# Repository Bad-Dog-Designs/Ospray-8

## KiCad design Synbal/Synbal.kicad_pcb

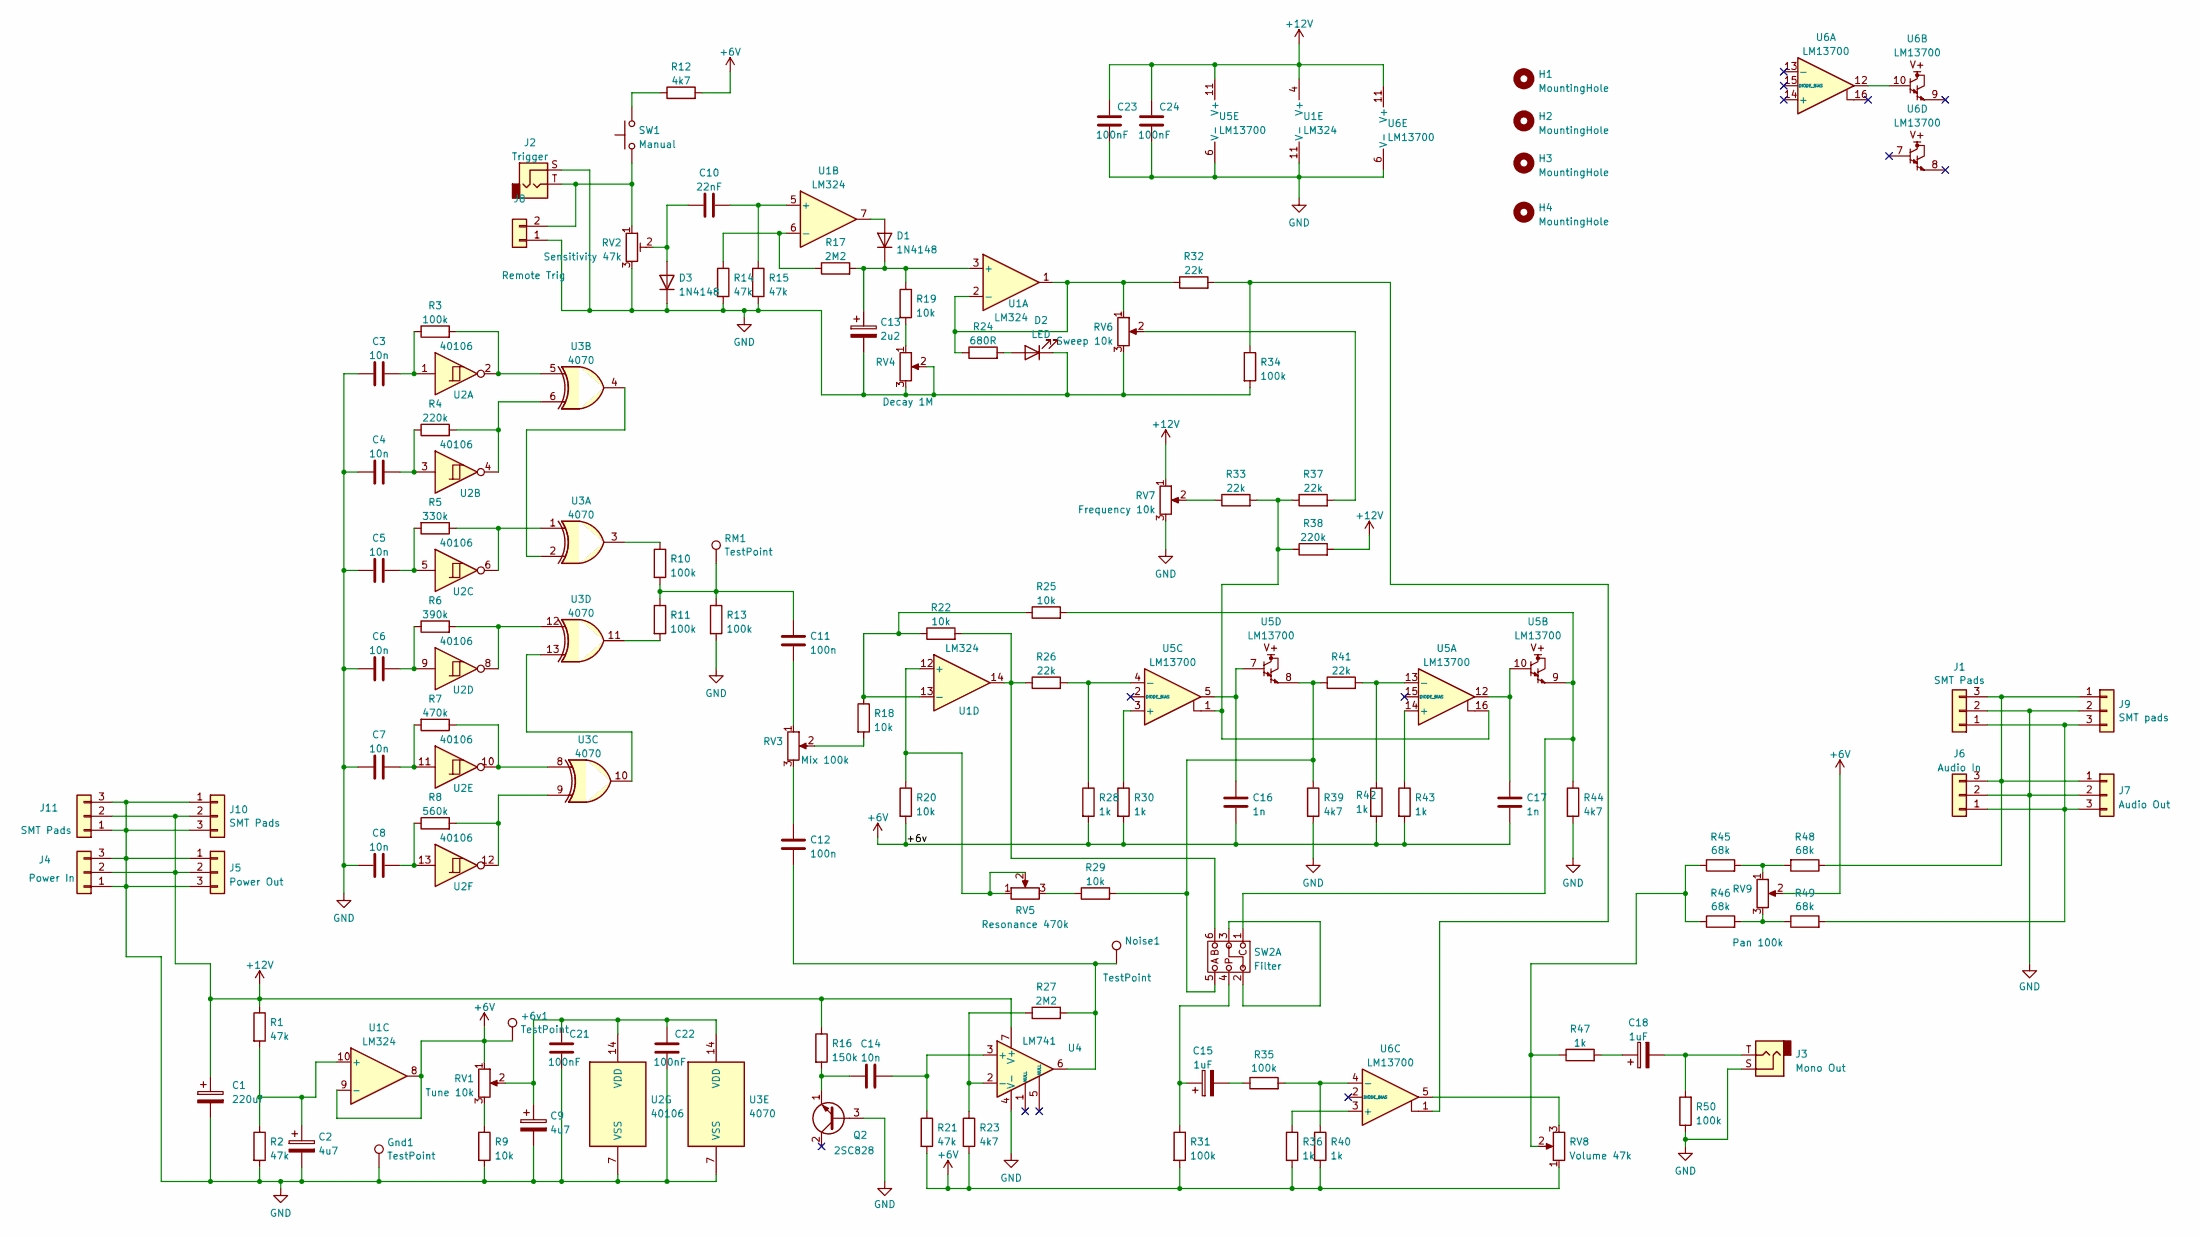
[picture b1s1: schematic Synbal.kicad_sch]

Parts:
+6v1: TestPoint; TestPoint_Keystone_5010-5014_Multipurpose
C1: 220uf; CP_Radial_D8.0mm_P3.50mm
C2, C9: 4u7; CP_Radial_D4.0mm_P1.50mm
C3, C4, C5, C6, C7, C8, C14: 10n; C_Disc_D7.0mm_W2.5mm_P5.00mm
C10: 22nF; C_Disc_D7.0mm_W2.5mm_P5.00mm
C11, C12: 100n; C_Disc_D7.0mm_W2.5mm_P5.00mm
C13: 2u2; CP_Radial_D4.0mm_P1.50mm
C15, C18: 1uF; CP_Radial_D4.0mm_P1.50mm
C16, C17: 1n; C_Disc_D7.0mm_W2.5mm_P5.00mm
C21, C22, C23, C24: 100nF; C_0805_2012Metric
D1, D3: 1N4148; D_MiniMELF
D2: LED; LED_D3.0mm
Gnd1: TestPoint; TestPoint_Keystone_5010-5014_Multipurpose
H1, H2, H3, H4: MountingHole; MountingHole_3.2mm_M3_ISO7380_Pad
J1, J10, J11: SMT Pads; Bus Connector
J2: Trigger; Jack_3.5mm_QingPu_WQP-PJ398SM_Vertical_CircularHoles
J3: Mono Out; Jack_3.5mm_QingPu_WQP-PJ398SM_Vertical_CircularHoles
J4: Power In; PinHeader_1x03_P2.54mm_Horizontal
J5: Power Out; PinHeader_1x03_P2.54mm_Horizontal
J6: Audio In; PinHeader_1x03_P2.54mm_Horizontal
J7: Audio Out; PinHeader_1x03_P2.54mm_Horizontal
J8: Remote Trig; PinHeader_1x02_P2.54mm_Vertical
J9: SMT pads; Bus Connector
Noise1: TestPoint; TestPoint_Keystone_5010-5014_Multipurpose
Q2: 2SC828; TO-92_Inline
R1, R2, R14, R15, R21: 47k; R_1206_3216Metric
R3, R10, R11, R13, R31, R34, R35, R50: 100k; R_1206_3216Metric
R4, R38: 220k; R_1206_3216Metric
R5: 330k; R_1206_3216Metric
R6: 390k; R_1206_3216Metric
R7: 470k; R_1206_3216Metric
R8: 560k; R_1206_3216Metric
R9, R18, R19, R20, R22, R25, R29: 10k; R_1206_3216Metric
R12, R23, R39, R44: 4k7; R_1206_3216Metric
R16: 150k; R_1206_3216Metric
R17, R27: 2M2; R_1206_3216Metric
R24: 680R; R_1206_3216Metric
R26, R32, R33, R37, R41: 22k; R_1206_3216Metric
R28, R30, R36, R40, R42, R43, R47: 1k; R_1206_3216Metric
R45, R46, R48, R49: 68k; R_1206_3216Metric
RM1: TestPoint; TestPoint_Keystone_5010-5014_Multipurpose
RV1: Tune 10k; Potentiometer_Alps_RK09K_Single_Vertical
RV2: Sensitivity 47k; Potentiometer_Piher_PT-6-V_Vertical
RV3: Mix 100k; Potentiometer_Alps_RK09K_Single_Vertical
RV4: Decay 1M; Potentiometer_Alps_RK09K_Single_Vertical
RV5: Resonance 470k; Potentiometer_Alps_RK09K_Single_Vertical
RV6: Sweep 10k; Potentiometer_Alps_RK09K_Single_Vertical
RV7: Frequency 10k; Potentiometer_Alps_RK09K_Single_Vertical
RV8: Volume 47k; Potentiometer_Alps_RK09K_Single_Vertical
RV9: Pan 100k; Potentiometer_Alps_RK09K_Single_Vertical
SW1: Manual; SW_PUSH_6mm_H5mm
SW2: Filter; 1P3WSW
U1: LM324; SOIC-14_3.9x8.7mm_P1.27mm
U2: 40106; SO-14_3.9x8.65mm_P1.27mm
U3: 4070; SO-14_3.9x8.65mm_P1.27mm
U4: LM741; SOIC-8_3.9x4.9mm_P1.27mm
U5, U6: LM13700; SOIC-16_3.9x9.9mm_P1.27mm

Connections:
+6V: +6v1.1, C16.2, C17.2, R12.2, R20.2, R21.2, R23.2, R28.2, R30.2, R31.2, R36.2, R40.2, R42.2, R43.2, RV1.1, RV8.1, RV9.2, U1.8, U1.9 (-); also elsewhere on the board
+12V: C1.1, C23.1, C24.1, J4.2, J5.2, J10.2, J11.2, R1.1, R16.1, R38.2, RV7.1, U1.4 (V+), U4.7 (V+), U5.11 (V+), U6.11 (V+)
GND: C1.2, C2.2, C3.1, C4.1, C5.1, C6.1, C7.1, C8.1, C9.2, C13.2, C21.2, C22.2, C23.2, C24.2, D2.1 (K), D3.1 (K), Gnd1.1, H1.1, H2.1, H3.1, H4.1, J1.2, J2.S, J3.S, J4.1, J4.3, J5.1, J5.3, J6.2, J7.2, J8.1, J9.2, J10.1, J10.3, J11.1, J11.3, Q2.3 (B), R2.2, R9.2, R13.2, R14.2, R15.2, R34.2, R39.2, R44.2, R50.1, RV1.MP, RV2.3, RV3.MP, RV4.2, RV4.3, RV4.MP, RV5.MP, RV6.3, RV6.MP, RV7.3, RV7.MP, RV8.MP, RV9.MP, U1.11 (V-), U2.7 (VSS), U3.7 (VSS), U4.4 (V-), U5.6 (V-), U6.6 (V-); also elsewhere on the board
unnamed: C3.2, R3.1, U2.1
unnamed: C4.2, R4.1, U2.3
unnamed: C5.2, R5.2, U2.5
unnamed: C6.2, R6.1, U2.9
unnamed: C7.2, R7.2, U2.11
unnamed: C8.2, R8.1, U2.13
unnamed 9: C11.1, R10.2, R11.1, R13.1, RM1.1; also elsewhere on the board
unnamed: C11.2, RV3.1
unnamed: C12.1, RV3.3
unnamed 12: C12.2, Noise1.1, R27.2, U4.6; also elsewhere on the board
unnamed: C15.1, R31.1, SW2.4
unnamed: C15.2, R35.1
unnamed: C16.1, U5.5, U5.7
unnamed: C17.1, U5.10, U5.12
unnamed: C18.1, R47.2
unnamed: C18.2, J3.T, R50.2
unnamed: D1.2 (A), U1.7
unnamed: C13.1, D1.1 (K), R17.2, R19.1, U1.3 (+)
unnamed: D2.2 (A), R24.2
unnamed: C10.1, D3.2 (A), RV2.2
unnamed: J1.1, J6.1, J7.3, J9.3, R49.2
unnamed: J1.3, J6.3, J7.1, J9.1, R48.1
unnamed: J2.T, J8.2, RV2.1, SW1.1
unnamed: C14.1, Q2.1 (E), R16.2
unnamed: R3.2, U2.2, U3.5
unnamed: R4.2, U2.4, U3.6
unnamed: R5.1, U2.6, U3.1
unnamed: R6.2, U2.8, U3.12
unnamed: R7.1, U2.10, U3.8
unnamed: R8.2, U2.12, U3.9
unnamed: R9.1, RV1.3
unnamed: R10.1, U3.3
unnamed: R11.2, U3.11
unnamed: R12.1, SW1.2
unnamed: R18.2, RV3.2
unnamed: R19.2, RV4.1
unnamed: R22.2, R26.1, SW2.6, U1.14
unnamed: R25.2, R44.1, SW2.1, U5.9
unnamed: R29.1, RV5.3
unnamed: R29.2, R39.1, R41.1, SW2.5, U5.8
unnamed: R32.2, R34.1, U6.1
unnamed: R33.1, RV7.2
unnamed: R33.2, R37.1, R38.1, U5.1, U5.16
unnamed: R37.2, RV6.2
unnamed: R45.1, R46.1, R47.1, RV8.2
unnamed: R45.2, R48.2, RV9.1
unnamed: R46.2, R49.1, RV9.3
unnamed: RV8.3, U6.5
unnamed: SW2.2, SW2.3
unnamed: R24.1, R32.1, RV6.1, U1.1, U1.2 (-)
unnamed: C10.2, R15.1, U1.5 (+)
unnamed: R14.1, R17.1, U1.6 (-)
unnamed: C2.1, R1.2, R2.1, U1.10 (+)
unnamed: R20.1, RV5.1, RV5.2, U1.12 (+)
unnamed: R18.1, R22.1, R25.1, U1.13 (-)
unnamed: C9.1, C21.1, C22.1, RV1.2, U2.14 (VDD), U3.14 (VDD)
unnamed: U3.2, U3.4
unnamed: U3.10, U3.13
unnamed: C14.2, R21.1, U4.3 (+)
unnamed: R23.1, R27.1, U4.2 (-)
unnamed: R43.1, U5.14 (+)
unnamed: R41.2, R42.1, U5.13 (-)
unnamed: R30.1, U5.3 (+)
unnamed: R26.2, R28.1, U5.4 (-)
unnamed: U6.10, U6.12
unnamed: R36.1, U6.3 (+)
unnamed: R35.2, R40.1, U6.4 (-)

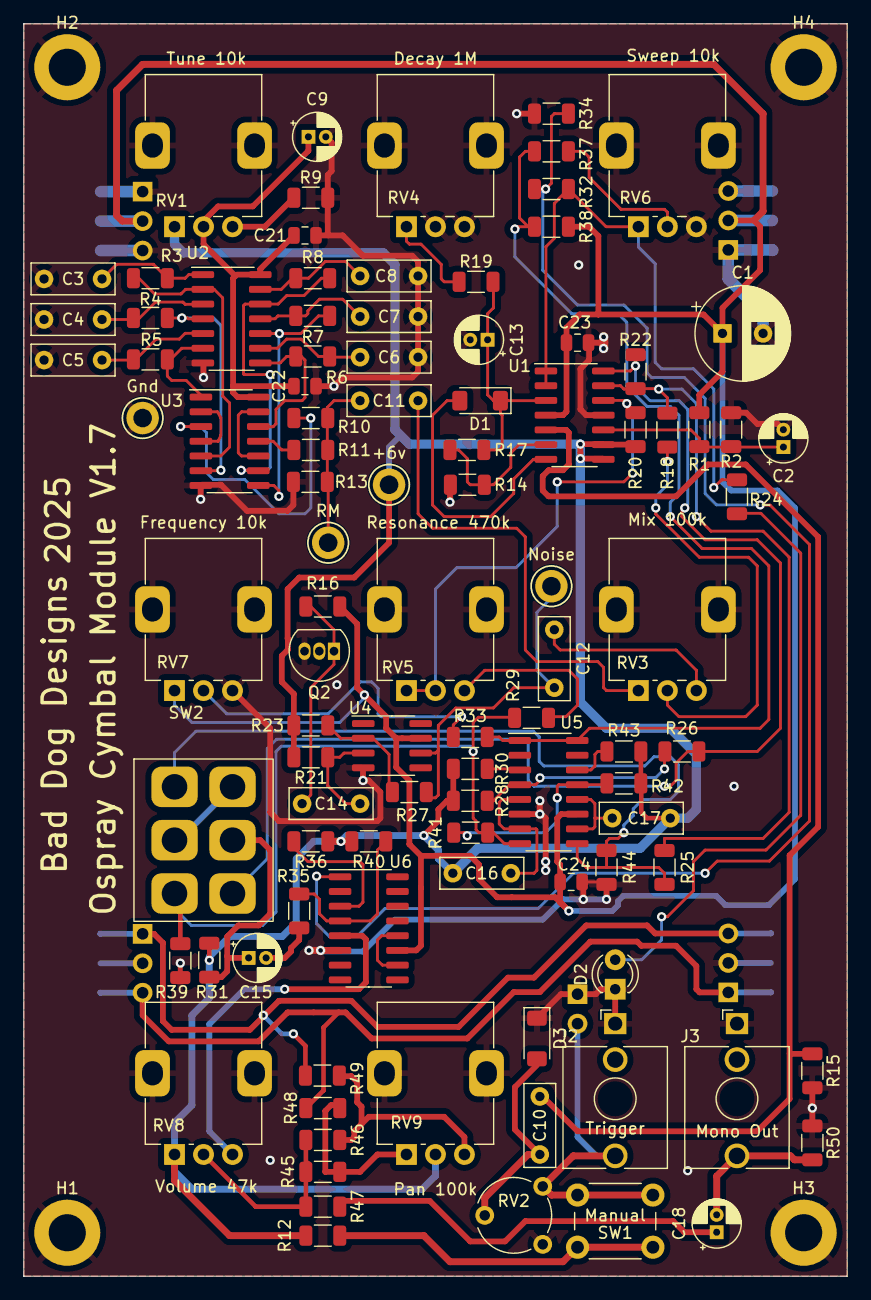
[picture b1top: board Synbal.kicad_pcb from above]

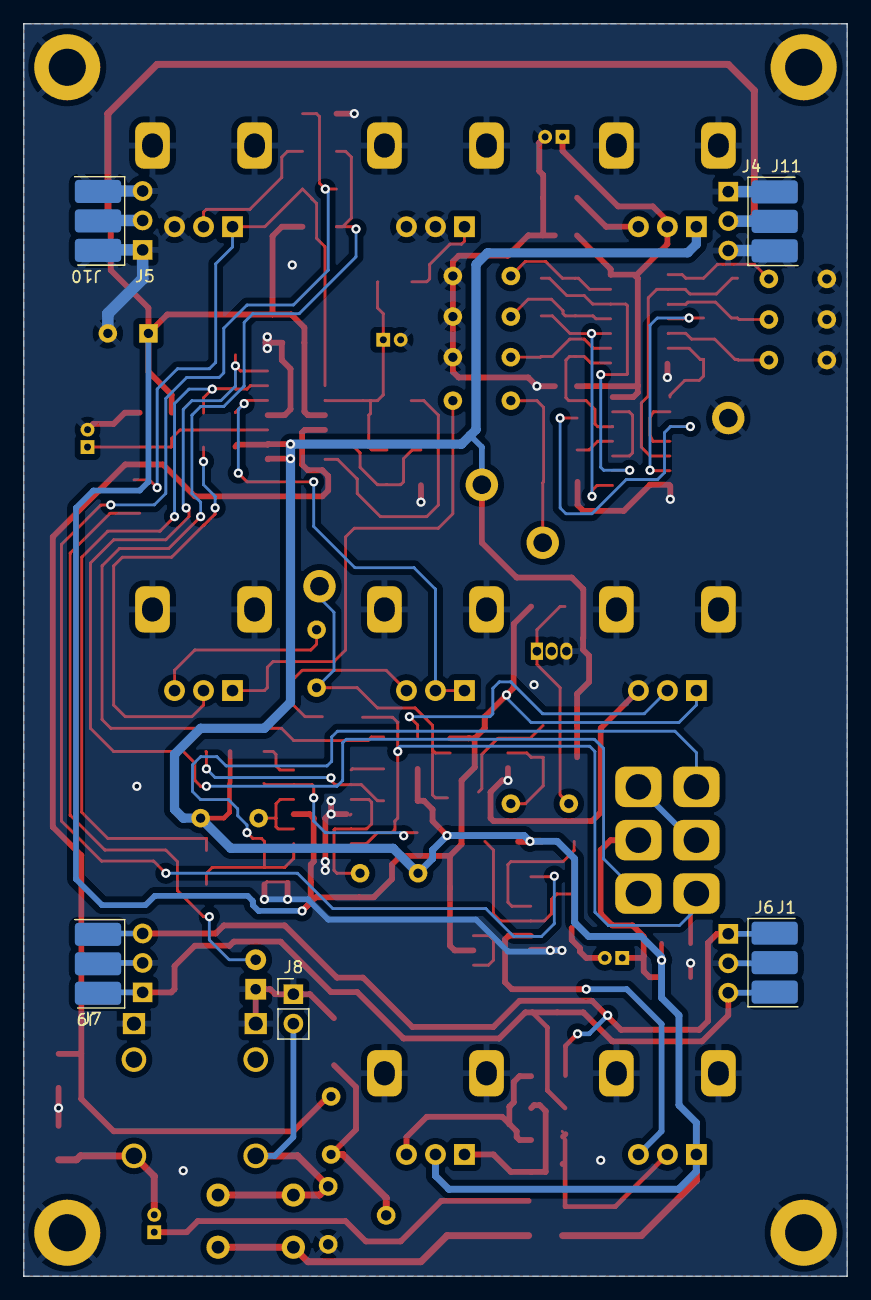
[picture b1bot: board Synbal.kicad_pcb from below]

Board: 2 copper layers, 71.0 x 108.0 mm, 112 parts (9 on the bottom side), 70 nets.

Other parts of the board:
+6v: TestPoint; TestPoint_Keystone_5010-5014_Multipurpose
Gnd: TestPoint; TestPoint_Keystone_5010-5014_Multipurpose
Noise: TestPoint; TestPoint_Keystone_5010-5014_Multipurpose
RM: TestPoint; TestPoint_Keystone_5010-5014_Multipurpose

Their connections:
+6V: +6v.1; also elsewhere on the board
GND: Gnd.1; also elsewhere on the board
unnamed 9: RM.1; also elsewhere on the board
unnamed 12: Noise.1; also elsewhere on the board

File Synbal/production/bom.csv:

Designator,Footprint,Quantity,Value,LCSC Part #
"+6V, GND, NOISE, RM",TestPoint_Keystone_5010-5014_Multipurpose,4,TestPoint,
C1,CP_Radial_D8.0mm_P3.50mm,1,220uf,
C10,C_Disc_D7.0mm_W2.5mm_P5.00mm,1,22nF,
"C11, C12",C_Disc_D7.0mm_W2.5mm_P5.00mm,2,100n,
C13,CP_Radial_D4.0mm_P1.50mm,1,2u2,
"C14, C3, C4, C5, C6, C7, C8",C_Disc_D7.0mm_W2.5mm_P5.00mm,7,10n,
"C15, C18",CP_Radial_D4.0mm_P1.50mm,2,1uF,
"C16, C17",C_Disc_D7.0mm_W2.5mm_P5.00mm,2,1n,
"C2, C9",CP_Radial_D4.0mm_P1.50mm,2,4u7,
"C21, C22, C23, C24",0805,4,100nF,
"D1, D3",D_MiniMELF,2,1N4148,
D2,LED_D3.0mm,1,LED,
"H1, H2, H3, H4",MountingHole_3.2mm_M3_ISO7380_Pad,4,MountingHole,
"J1, J10, J11, J9",Bus Connector,4,SMT Pads,
J2,Jack_3.5mm_QingPu_WQP-PJ398SM_Vertical_CircularHoles,1,Trigger,
J3,Jack_3.5mm_QingPu_WQP-PJ398SM_Vertical_CircularHoles,1,Mono Out,
J4,PinHeader_1x03_P2.54mm_Horizontal,1,Power In,
J5,PinHeader_1x03_P2.54mm_Horizontal,1,Power Out,
J6,PinHeader_1x03_P2.54mm_Horizontal,1,Audio In,
J7,PinHeader_1x03_P2.54mm_Horizontal,1,Audio Out,
J8,PinHeader_1x02_P2.54mm_Vertical,1,Remote Trig,
Q2,TO-92_Inline,1,2SC828,
"R1, R14, R15, R2, R21",1206,5,47k,
"R10, R11, R13, R3, R31, R34, R35, R50",1206,8,100k,
"R12, R23, R39, R44",1206,4,4k7,
R16,1206,1,150k,
"R17, R27",1206,2,2M2,
"R18, R19, R20, R22, R25, R29, R9",1206,7,10k,
R24,1206,1,680R,
"R26, R32, R33, R37, R41",1206,5,22k,
"R28, R30, R36, R40, R42, R43, R47",1206,7,1k,
"R38, R4",1206,2,220k,
"R45, R46, R48, R49",1206,4,68k,
R5,1206,1,330k,
R6,1206,1,390k,
R7,1206,1,470k,
R8,1206,1,560k,
RV1,Potentiometer_Alps_RK09K_Single_Vertical,1,Tune 10k,
RV2,Potentiometer_Piher_PT-6-V_Vertical,1,Sensitivity 47k,
RV3,Potentiometer_Alps_RK09K_Single_Vertical,1,Mix 100k,
RV4,Potentiometer_Alps_RK09K_Single_Vertical,1,Decay 1M,
RV5,Potentiometer_Alps_RK09K_Single_Vertical,1,Resonance 470k,
RV6,Potentiometer_Alps_RK09K_Single_Vertical,1,Sweep 10k,
RV7,Potentiometer_Alps_RK09K_Single_Vertical,1,Frequency 10k,
RV8,Potentiometer_Alps_RK09K_Single_Vertical,1,Volume 47k,
RV9,Potentiometer_Alps_RK09K_Single_Vertical,1,Pan 100k,
SW1,SW_PUSH_6mm_H5mm,1,Manual,
SW2,1P3WSW,1,Filter,
U1,SOIC-14_3.9x8.7mm_P1.27mm,1,LM324,
U2,SO-14_3.9x8.65mm_P1.27mm,1,40106,
U3,SO-14_3.9x8.65mm_P1.27mm,1,4070,
U4,SOIC-8_3.9x4.9mm_P1.27mm,1,LM741,
"U5, U6",SOIC-16_3.9x9.9mm_P1.27mm,2,LM13700,

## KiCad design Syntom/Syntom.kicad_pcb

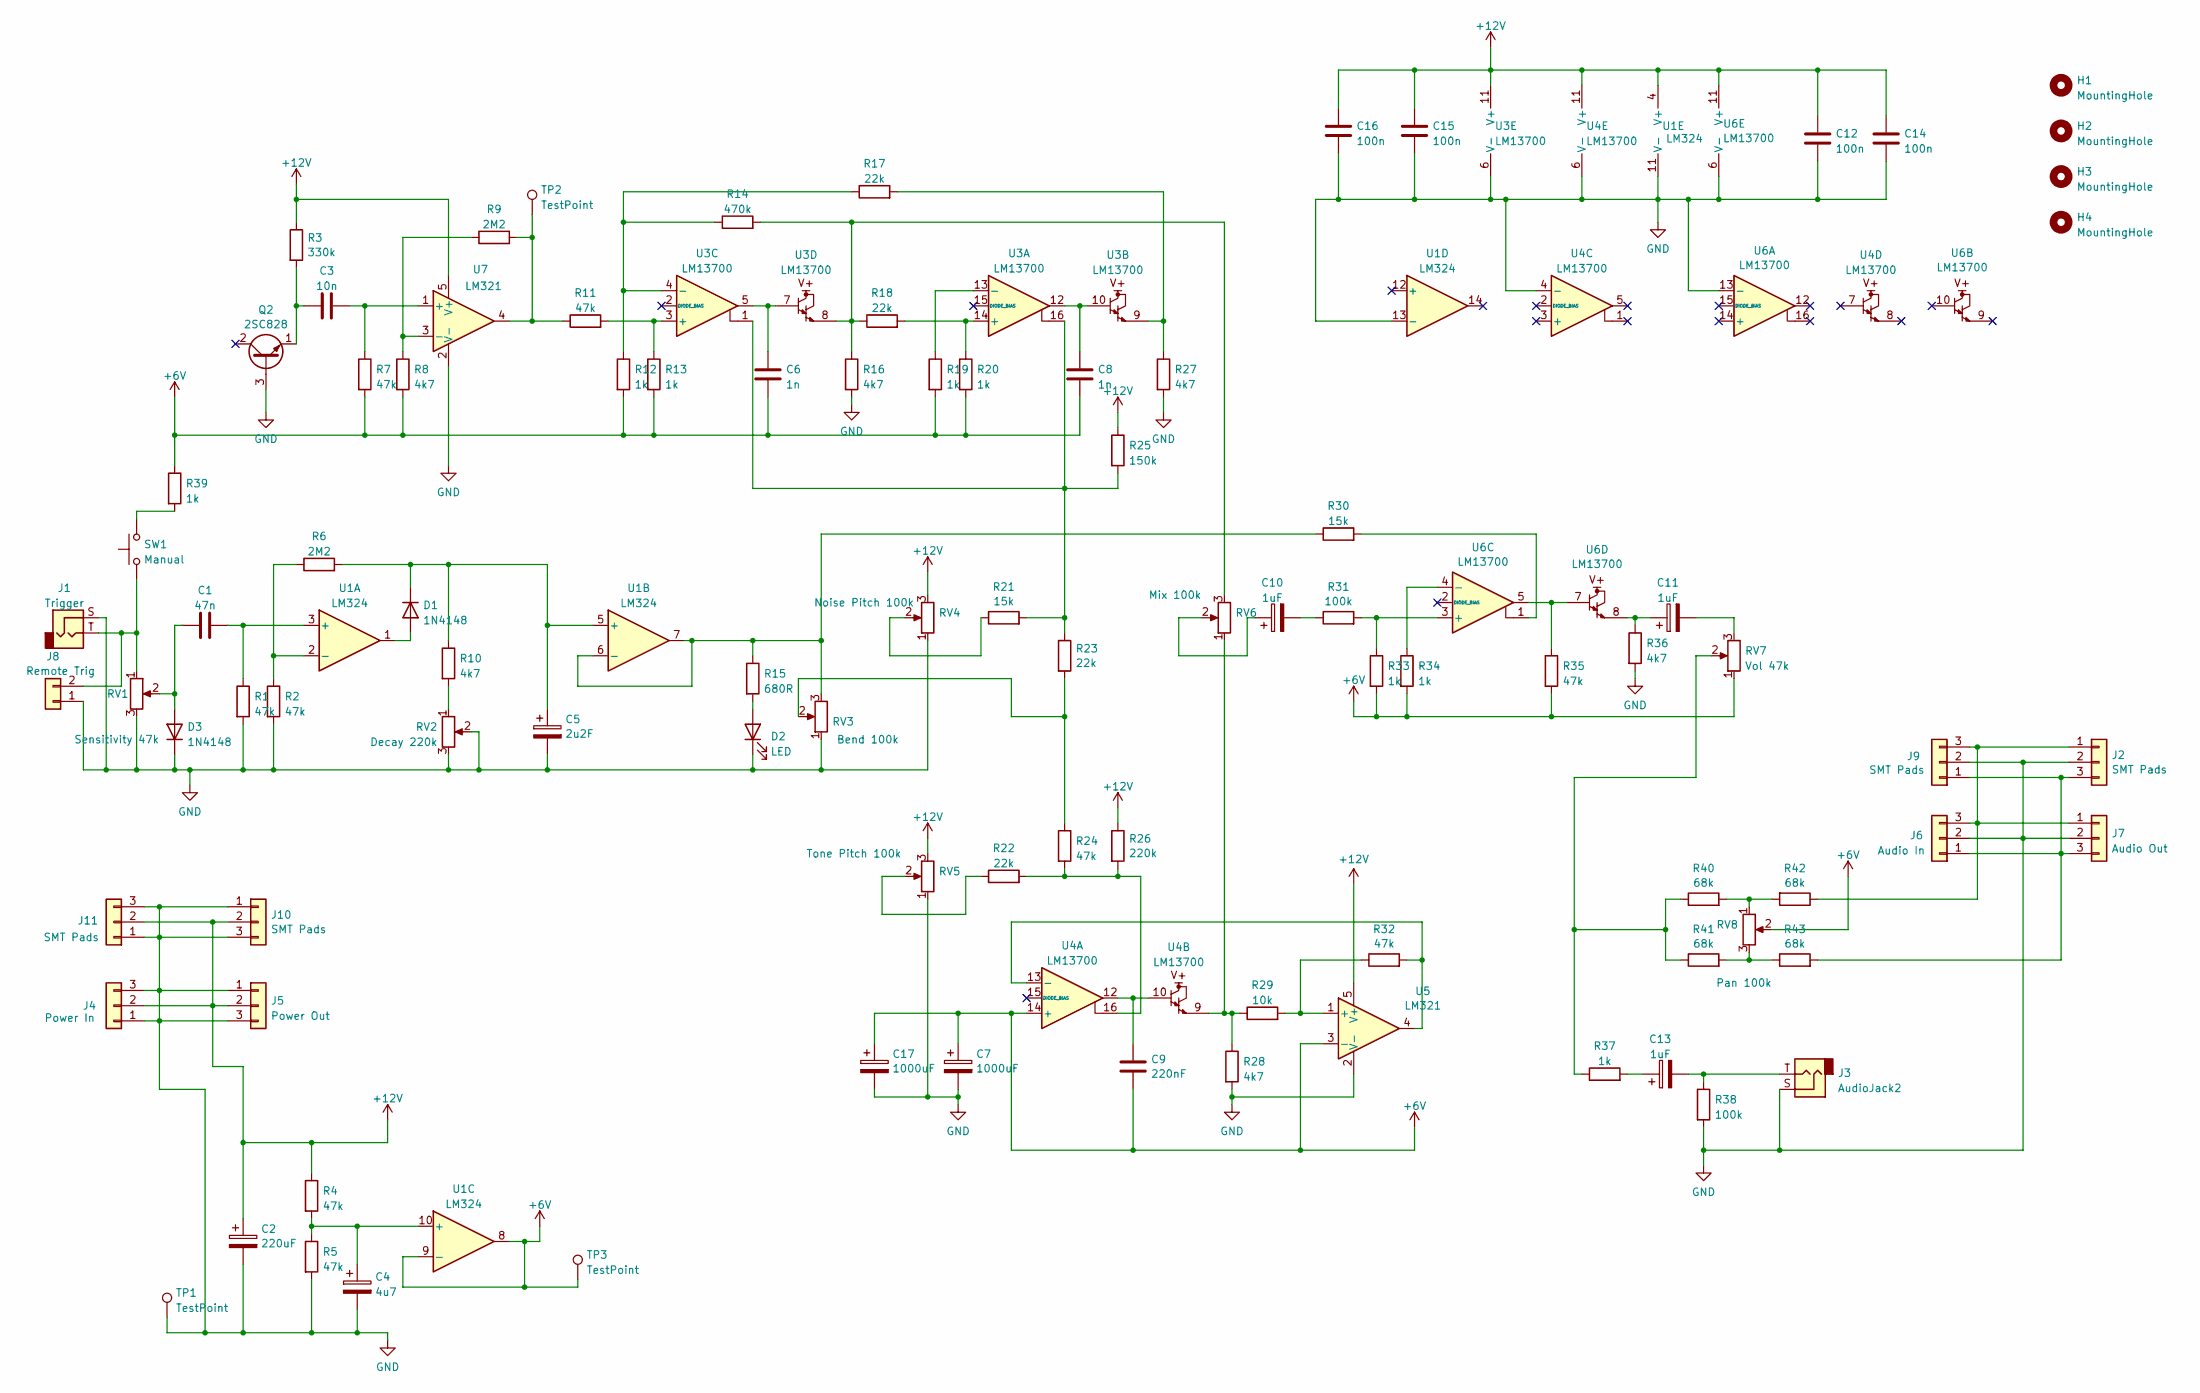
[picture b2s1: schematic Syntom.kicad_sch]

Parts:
C1: 47n; C_Disc_D4.3mm_W1.9mm_P5.00mm
C2: 220uF; CP_Radial_D8.0mm_P3.50mm
C3: 10n; C_Disc_D4.3mm_W1.9mm_P5.00mm
C4: 4u7; CP_Radial_D4.0mm_P1.50mm
C5: 2u2F; CP_Radial_D4.0mm_P1.50mm
C6, C8: 1n; C_Disc_D4.3mm_W1.9mm_P5.00mm
C7, C17: 1000uF; CP_Radial_D8.0mm_P3.50mm
C9: 220nF; C_Disc_D4.3mm_W1.9mm_P5.00mm
C10, C11, C13: 1uF; CP_Radial_D4.0mm_P1.50mm
C12, C14, C15, C16: 100n; C_0805_2012Metric
D1, D3: 1N4148; D_MiniMELF
D2: LED; LED_D3.0mm
H1, H2, H3, H4: MountingHole; MountingHole_3.2mm_M3_DIN965_Pad
J1: Trigger; Jack_3.5mm_QingPu_WQP-PJ398SM_Vertical_CircularHoles
J2, J9, J10, J11: SMT Pads; Bus Connector
J3: AudioJack2; Jack_3.5mm_QingPu_WQP-PJ398SM_Vertical_CircularHoles
J4: Power In; PinHeader_1x03_P2.54mm_Horizontal
J5: Power Out; PinHeader_1x03_P2.54mm_Horizontal
J6: Audio In; PinHeader_1x03_P2.54mm_Horizontal
J7: Audio Out; PinHeader_1x03_P2.54mm_Horizontal
J8: Remote Trig; PinHeader_1x02_P2.54mm_Vertical
Q2: 2SC828; TO-92_Inline
R1, R2, R4, R5, R7, R11, R24, R32, R35: 47k; R_1206_3216Metric
R3: 330k; R_1206_3216Metric
R6, R9: 2M2; R_1206_3216Metric
R8, R10, R16, R27, R28, R36: 4k7; R_1206_3216Metric
R12, R13, R19, R20, R33, R34, R37, R39: 1k; R_1206_3216Metric
R14: 470k; R_1206_3216Metric
R15: 680R; R_1206_3216Metric
R17, R18, R22, R23: 22k; R_1206_3216Metric
R21, R30: 15k; R_1206_3216Metric
R25: 150k; R_1206_3216Metric
R26: 220k; R_1206_3216Metric
R29: 10k; R_1206_3216Metric
R31, R38: 100k; R_1206_3216Metric
R40, R41, R42, R43: 68k; R_1206_3216Metric
RV1: Sensitivity 47k; Potentiometer_Piher_PT-6-V_Vertical
RV2: Decay 220k; Potentiometer_Alps_RK09K_Single_Vertical
RV3: Bend 100k; Potentiometer_Alps_RK09K_Single_Vertical
RV4: Noise Pitch 100k; Potentiometer_Alps_RK09K_Single_Vertical
RV5: Tone Pitch 100k; Potentiometer_Alps_RK09K_Single_Vertical
RV6: Mix 100k; Potentiometer_Alps_RK09K_Single_Vertical
RV7: Vol 47k; Potentiometer_Alps_RK09K_Single_Vertical
RV8: Pan 100k; Potentiometer_Alps_RK09K_Single_Vertical
SW1: Manual; SW_PUSH_6mm_H5mm
TP1, TP2, TP3: TestPoint; TestPoint_THTPad_D1.5mm_Drill0.7mm
U1: LM324; SO-14_3.9x8.65mm_P1.27mm
U3, U4, U6: LM13700; SO-16_3.9x9.9mm_P1.27mm
U5, U7: LM321; SOT-23-5

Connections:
+6V: C6.2, C7.1, C8.2, C9.2, C17.1, R7.2, R8.2, R12.2, R13.2, R19.2, R20.2, R33.2, R34.2, R35.2, R39.1, RV7.1, RV8.2, TP3.1, U1.8, U1.9 (-), U4.14 (+), U5.3 (-)
+12V: C2.1, C12.1, C14.1, C15.1, C16.1, J4.2, J5.2, J10.2, J11.2, R3.1, R4.1, R25.1, R26.1, RV4.3, RV5.3, U1.4 (V+), U3.11 (V+), U4.11 (V+), U5.5 (V+), U6.11 (V+), U7.5 (V+)
GND: C2.2, C4.2, C5.2, C7.2, C12.2, C14.2, C15.2, C16.2, C17.2, D2.1 (K), D3.1 (K), H1.1, H2.1, H3.1, H4.1, J1.S, J2.2, J3.S, J4.1, J4.3, J5.1, J5.3, J6.2, J7.2, J8.1, J9.2, J10.1, J10.3, J11.1, J11.3, Q2.3 (B), R1.2, R2.2, R5.2, R16.2, R27.2, R28.2, R36.2, R38.2, RV1.3, RV2.2, RV2.3, RV2.MP, RV3.1, RV3.MP, RV4.1, RV4.MP, RV5.1, RV5.MP, RV6.MP, RV7.MP, RV8.MP, TP1.1, U1.11 (V-), U1.13 (-), U3.6 (V-), U4.4 (-), U4.6 (V-), U5.2 (V-), U6.6 (V-), U6.13 (-), U7.2 (V-)
unnamed: C6.1, U3.5, U3.7
unnamed: C8.1, U3.10, U3.12
unnamed: C9.1, U4.10, U4.12
unnamed: C10.1, RV6.2
unnamed: C10.2, R31.1
unnamed: C11.1, R36.1, U6.8
unnamed: C11.2, RV7.3
unnamed: C13.1, R37.2
unnamed: C13.2, J3.T, R38.1
unnamed: D1.2 (A), U1.1
unnamed: C5.1, D1.1 (K), R6.2, R10.1, U1.5 (+)
unnamed: D2.2 (A), R15.2
unnamed: C1.1, D3.2 (A), RV1.2
unnamed: J2.1, J6.3, J7.1, J9.3, R42.1
unnamed: J2.3, J6.1, J7.3, J9.1, R43.2
unnamed: J1.T, J8.2, RV1.1, SW1.1
unnamed: C3.1, Q2.1 (E), R3.2
unnamed: R10.2, RV2.1
unnamed: R9.2, R11.1, TP2.1, U7.4
unnamed: R14.2, R16.1, R18.1, RV6.3, U3.8
unnamed: R17.2, R27.1, U3.9
unnamed: R21.1, RV4.2
unnamed: R21.2, R23.1, R25.2, U3.1, U3.16
unnamed: R22.1, RV5.2
unnamed: R22.2, R24.2, R26.2, U4.16
unnamed: R23.2, R24.1, RV3.2
unnamed: R28.1, R29.1, RV6.1, U4.9
unnamed: R30.2, U6.1
unnamed: R35.1, U6.5, U6.7
unnamed: R37.1, R40.1, R41.1, RV7.2
unnamed: R39.2, SW1.2
unnamed: R40.2, R42.2, RV8.1
unnamed: R41.2, R43.1, RV8.3
unnamed: C1.2, R1.1, U1.3 (+)
unnamed: R2.1, R6.1, U1.2 (-)
unnamed: R15.1, R30.1, RV3.3, U1.6 (-), U1.7
unnamed: C4.1, R4.2, R5.1, U1.10 (+)
unnamed: R18.2, R20.1, U3.14 (+)
unnamed: R19.1, U3.13 (-)
unnamed: R11.2, R13.1, U3.3 (+)
unnamed: R12.1, R14.1, R17.1, U3.4 (-)
unnamed: R32.2, U4.13 (-), U5.4
unnamed: R29.2, R32.1, U5.1 (+)
unnamed: R31.2, R33.1, U6.3 (+)
unnamed: R34.1, U6.4 (-)
unnamed: C3.2, R7.1, U7.1 (+)
unnamed: R8.1, R9.1, U7.3 (-)

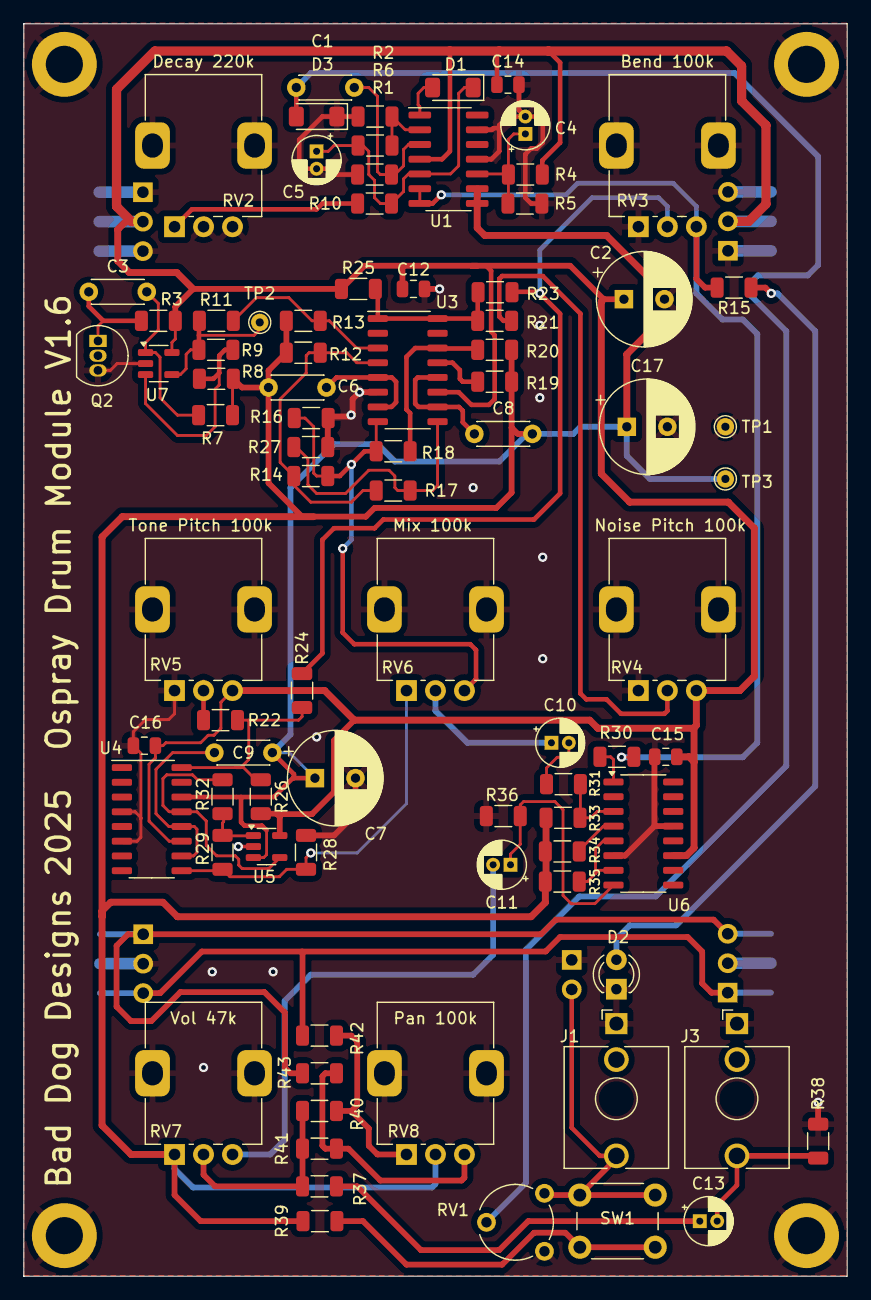
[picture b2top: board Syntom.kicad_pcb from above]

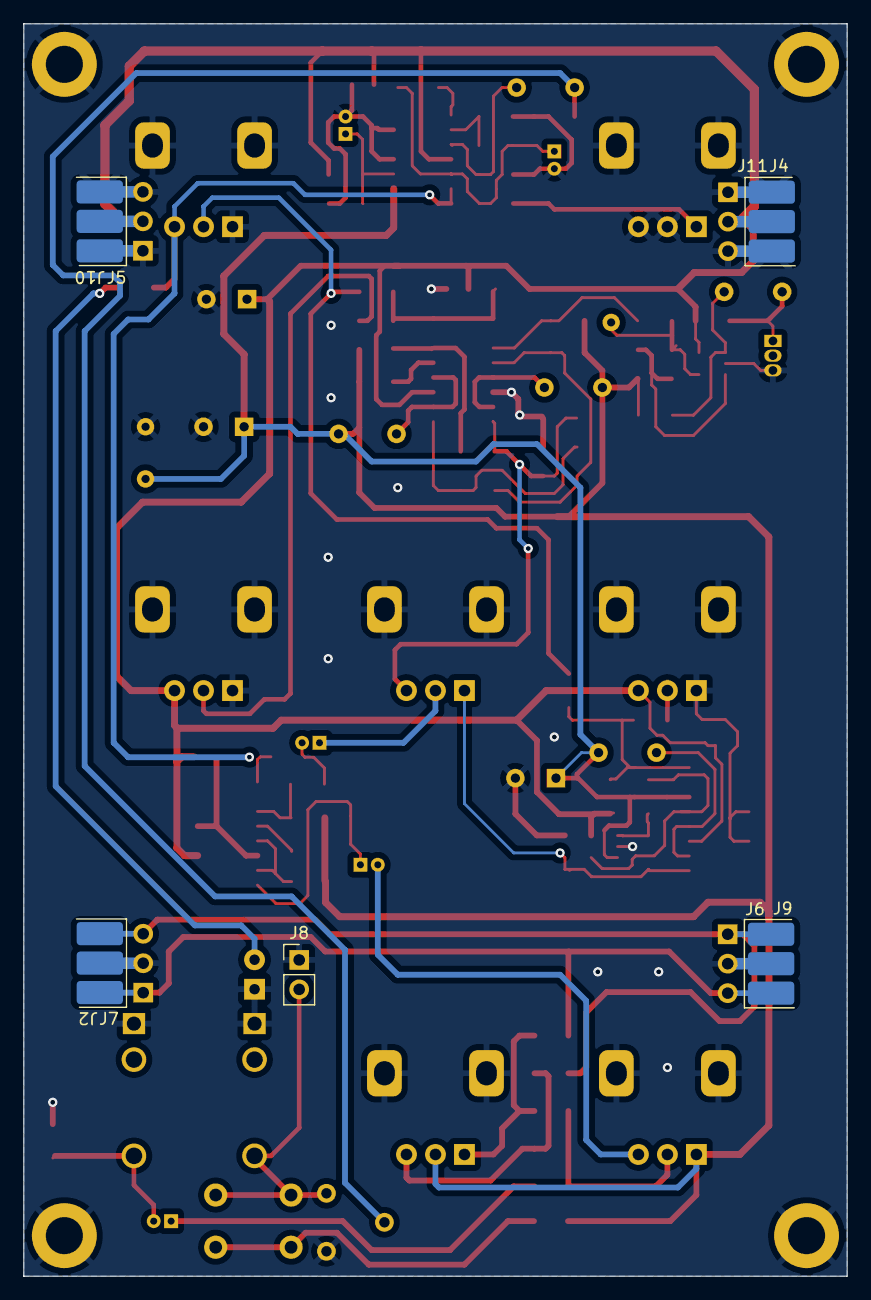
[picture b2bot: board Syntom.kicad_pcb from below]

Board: 2 copper layers, 71.0 x 108.0 mm, 97 parts (9 on the bottom side), 50 nets.

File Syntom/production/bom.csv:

Designator,Footprint,Quantity,Value,LCSC Part #
C1,C_Disc_D4.3mm_W1.9mm_P5.00mm,1,47n,
"C10, C11, C13",CP_Radial_D4.0mm_P1.50mm,3,1uF,
"C12, C14, C15, C16",0805,4,100n,
"C17, C7",CP_Radial_D8.0mm_P3.50mm,2,1000uF,
C2,CP_Radial_D8.0mm_P3.50mm,1,220uF,
C3,C_Disc_D4.3mm_W1.9mm_P5.00mm,1,10n,
C4,CP_Radial_D4.0mm_P1.50mm,1,4u7,
C5,CP_Radial_D4.0mm_P1.50mm,1,2u2F,
"C6, C8",C_Disc_D4.3mm_W1.9mm_P5.00mm,2,1n,
C9,C_Disc_D4.3mm_W1.9mm_P5.00mm,1,220nF,
"D1, D3",D_MiniMELF,2,1N4148,
D2,LED_D3.0mm,1,LED,
"H1, H2, H3, H4",MountingHole_3.2mm_M3_DIN965_Pad,4,MountingHole,
J1,Jack_3.5mm_QingPu_WQP-PJ398SM_Vertical_CircularHoles,1,Trigger,
"J10, J11, J2, J9",Bus Connector,4,SMT Pads,
J3,Jack_3.5mm_QingPu_WQP-PJ398SM_Vertical_CircularHoles,1,AudioJack2,
J4,PinHeader_1x03_P2.54mm_Horizontal,1,Power In,
J5,PinHeader_1x03_P2.54mm_Horizontal,1,Power Out,
J6,PinHeader_1x03_P2.54mm_Horizontal,1,Audio In,
J7,PinHeader_1x03_P2.54mm_Horizontal,1,Audio Out,
J8,PinHeader_1x02_P2.54mm_Vertical,1,Remote Trig,
Q2,TO-92_Inline,1,2SC828,
"R1, R11, R2, R24, R32, R35, R4, R5, R7",1206,9,47k,
"R10, R16, R27, R28, R36, R8",1206,6,4k7,
"R12, R13, R19, R20, R33, R34, R37, R39",1206,8,1k,
R14,1206,1,470k,
R15,1206,1,680R,
"R17, R18, R22, R23",1206,4,22k,
"R21, R30",1206,2,15k,
R25,1206,1,150k,
R26,1206,1,220k,
R29,1206,1,10k,
R3,1206,1,330k,
"R31, R38",1206,2,100k,
"R40, R41, R42, R43",1206,4,68k,
"R6, R9",1206,2,2M2,
RV1,Potentiometer_Piher_PT-6-V_Vertical,1,Sensitivity 47k,
RV2,Potentiometer_Alps_RK09K_Single_Vertical,1,Decay 220k,
RV3,Potentiometer_Alps_RK09K_Single_Vertical,1,Bend 100k,
RV4,Potentiometer_Alps_RK09K_Single_Vertical,1,Noise Pitch 100k,
RV5,Potentiometer_Alps_RK09K_Single_Vertical,1,Tone Pitch 100k,
RV6,Potentiometer_Alps_RK09K_Single_Vertical,1,Mix 100k,
RV7,Potentiometer_Alps_RK09K_Single_Vertical,1,Vol 47k,
RV8,Potentiometer_Alps_RK09K_Single_Vertical,1,Pan 100k,
SW1,SW_PUSH_6mm_H5mm,1,Manual,
"TP1, TP2, TP3",TestPoint_THTPad_D1.5mm_Drill0.7mm,3,TestPoint,
U1,SO-14_3.9x8.65mm_P1.27mm,1,LM324,
"U3, U4, U6",SO-16_3.9x9.9mm_P1.27mm,3,LM13700,
"U5, U7",SOT-23-5,2,LM321,
